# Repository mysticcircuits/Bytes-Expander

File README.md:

# Bytes-Expander
Variable Loop Length Turing Machine Expander

A 3rd party Turing Machine expander which allows for voltage control over the loop length of the host device.  It will require 
some modifications to the host Turing Machine which have only been tested with the Turing v1, but it is hypothetically
possible to modify the v2 to do accept the expander too.  There are instructions for the v1 modifications in the instructions
folder.

For questions or help building the module check out the relevant thread on MW.

http://www.muffwiggler.com/forum/viewtopic.php?p=1646194#1646194

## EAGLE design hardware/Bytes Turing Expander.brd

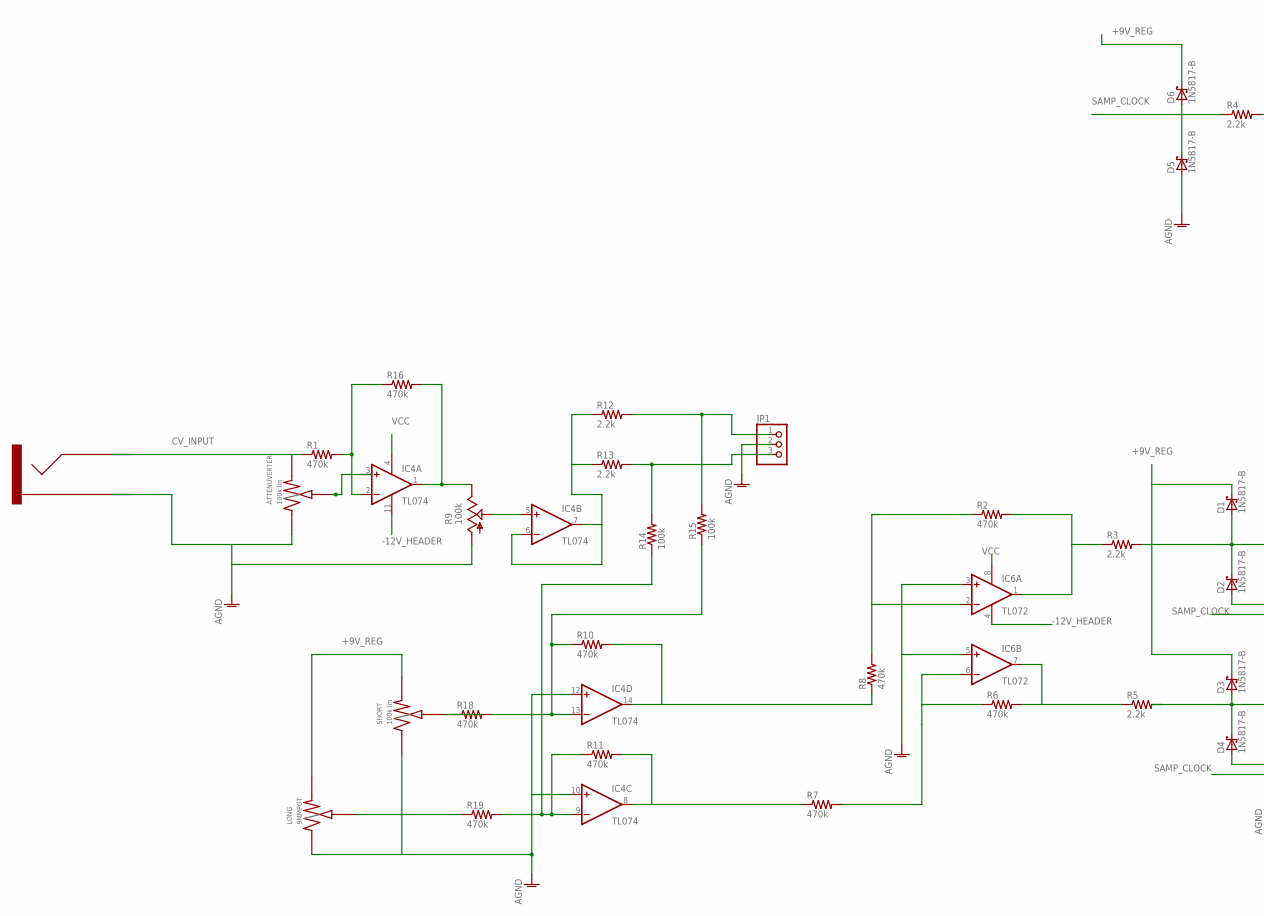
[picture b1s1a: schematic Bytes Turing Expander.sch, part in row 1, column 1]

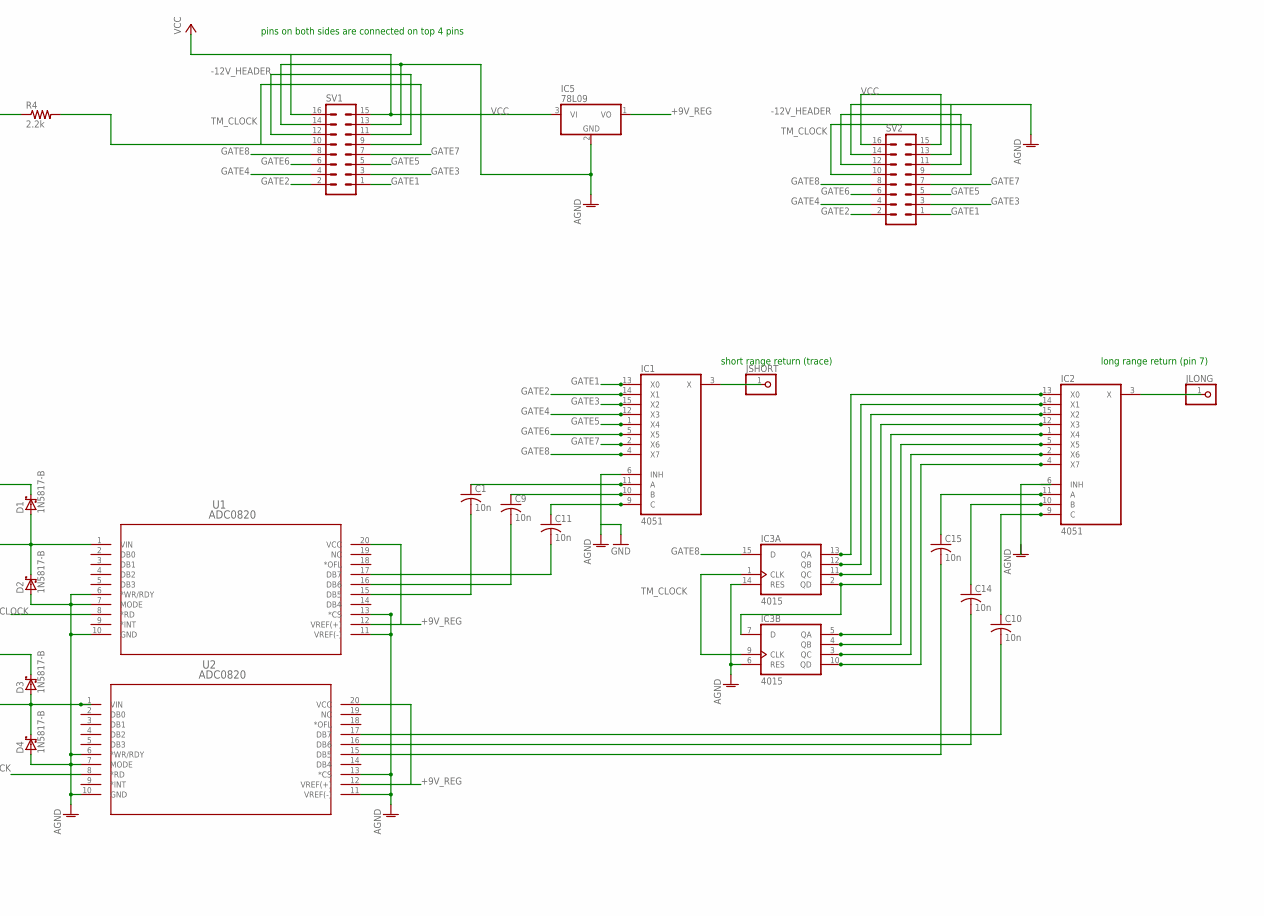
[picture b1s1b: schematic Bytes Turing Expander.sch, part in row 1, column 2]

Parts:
ATTENUVERTER: 100k lin; 9MMPOT
C1, C9, C10, C11, C14, C15: 10n; C025-024X044
D1, D2, D3, D4, D5, D6: 1N5817-B; DO41-7.6
IC1, IC2: 4051; DIL16
IC3: 4015; DIL16
IC4: TL074; DIL14
IC5: 78L09; TO92
IC6: TL072; DIL08
JLONG: PINHD-1X1; 1X01
JP1: PINHD-1X3; 1X03
JSHORT: PINHD-1X1; 1X01
LONG: 9MMPOT
R1, R2, R6, R7, R8, R10, R11, R16, R18, R19: 470k; 0204V
R3, R4, R5, R12, R13: 2.2k; 0204V
R9: 100k; B64Y
R14, R15: 100k; 0204V
SHORT: 100k lin; 9MMPOT
SV1, SV2: MA08-2
U1, U2: ADC0820; NFH20
U$1: 3.5MMJACK; 3.5MMPHONEJACK

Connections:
+9V_REG: D1.C, D3.C, D6.C, IC5.1 (VO), LONG.LEFT (RIGHT), SHORT.LEFT (RIGHT), U1.12 (VREF(+)), U1.20 (VCC), U2.12 (VREF(+)), U2.20 (VCC)
-12V_HEADER: IC4.11 (V-), IC6.4 (V-), SV1.11, SV1.12, SV2.11, SV2.12
AGND: ATTENUVERTER.RIGHT (LEFT), D2.A, D4.A, D5.A, IC1.6 (INH), IC1.7 (VEE), IC1.8 (GND), IC2.7 (VEE), IC2.8 (GND), IC3.6 (RES), IC3.14 (RES), IC4.10 (+IN), IC4.12 (+IN), IC5.2 (GND), IC6.3 (+IN), IC6.5 (+IN), JP1.2, LONG.RIGHT (LEFT), R9.A, SHORT.RIGHT (LEFT), SV1.13, SV1.14, SV2.13, SV2.14, U1.6 (*WR/RDY), U1.7 (MODE), U1.10 (GND), U1.11 (VREF(-)), U1.13 (*CS), U2.6 (*WR/RDY), U2.7 (MODE), U2.10 (GND), U2.11 (VREF(-)), U2.13 (*CS), U$1.SLEEVE
CV_INPUT: ATTENUVERTER.LEFT (RIGHT), R1.1, U$1.TIP
GATE1: IC1.13 (X0), SV1.1, SV2.1
GATE2: IC1.14 (X1), SV1.2, SV2.2
GATE3: IC1.15 (X2), SV1.3, SV2.3
GATE4: IC1.12 (X3), SV1.4, SV2.4
GATE5: IC1.1 (X4), SV1.5, SV2.5
GATE6: IC1.5 (X5), SV1.6, SV2.6
GATE7: IC1.2 (X6), SV1.7, SV2.7
GATE8: IC1.4 (X7), IC3.15 (D), SV1.8, SV2.8
JSHORT: IC1.3 (X), JSHORT.1
unnamed: IC4.2 (-IN), R1.2, R16.1
unnamed: IC4.1 (OUT), R9.E, R16.2
unnamed: LONG.CENTER, R19.1
unnamed: R18.1, SHORT.CENTER
unnamed: IC4.6 (-IN), IC4.7 (OUT), R12.1, R13.1
unnamed: IC4.5 (+IN), R9.S
unnamed: IC6.1 (OUT), R2.2, R3.1
unnamed: IC4.9 (-IN), R11.1, R14.1, R19.2
unnamed: IC2.12 (X3), IC3.2 (QD), IC3.7 (D)
unnamed: C11.1, IC1.9 (C)
unnamed: IC2.13 (X0), IC3.13 (QA)
unnamed: IC2.14 (X1), IC3.12 (QB)
unnamed: IC2.15 (X2), IC3.11 (QC)
unnamed: IC2.1 (X4), IC3.5 (QA)
unnamed: IC2.5 (X5), IC3.4 (QB)
unnamed: IC2.2 (X6), IC3.3 (QC)
unnamed: IC2.4 (X7), IC3.10 (QD)
unnamed: IC4.14 (OUT), R8.1, R10.2
unnamed: IC6.7 (OUT), R5.1, R6.2
unnamed: IC4.8 (OUT), R7.1, R11.2
unnamed: JP1.3, R13.2, R14.2
unnamed: C9.1, IC1.10 (B)
unnamed: C1.1, IC1.11 (A)
unnamed: C11.2, U1.17 (DB7)
unnamed: C9.2, U1.16 (DB6)
unnamed: C1.2, U1.15 (DB5)
unnamed: C10.1, IC2.9 (C)
unnamed: C15.1, IC2.11 (A)
unnamed: C14.1, IC2.10 (B)
unnamed: IC6.2 (-IN), R2.1, R8.2
unnamed: C15.2, U2.15 (DB5)
unnamed: C14.2, U2.16 (DB6)
unnamed: C10.2, U2.17 (DB7)
unnamed: JP1.1, R12.2, R15.2
unnamed: ATTENUVERTER.CENTER, IC4.3 (+IN)
unnamed: IC4.13 (-IN), R10.1, R15.1, R18.2
unnamed: IC6.6 (-IN), R6.1, R7.2
unnamed: IC2.3 (X), JLONG.1
unnamed: D3.A, D4.C, R5.2, U2.1 (VIN)
unnamed: D1.A, D2.C, R3.2, U1.1 (VIN)
SAMP_CLOCK: D5.C, D6.A, R4.1, U1.8 (*RD), U2.8 (*RD)
TM_CLOCK: IC3.1 (CLK), IC3.9 (CLK), R4.2, SV1.9, SV1.10, SV2.9, SV2.10
VCC: IC1.16 (VCC), IC2.16 (VCC), IC3.16 (VDD), IC4.4 (V+), IC5.3 (VI), IC6.8 (V+), SV1.15, SV1.16, SV2.15, SV2.16
VSS: IC3.8 (VSS)

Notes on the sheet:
short range return (trace)
long range return (pin 7)
pins on both sides are connected on top 4 pins

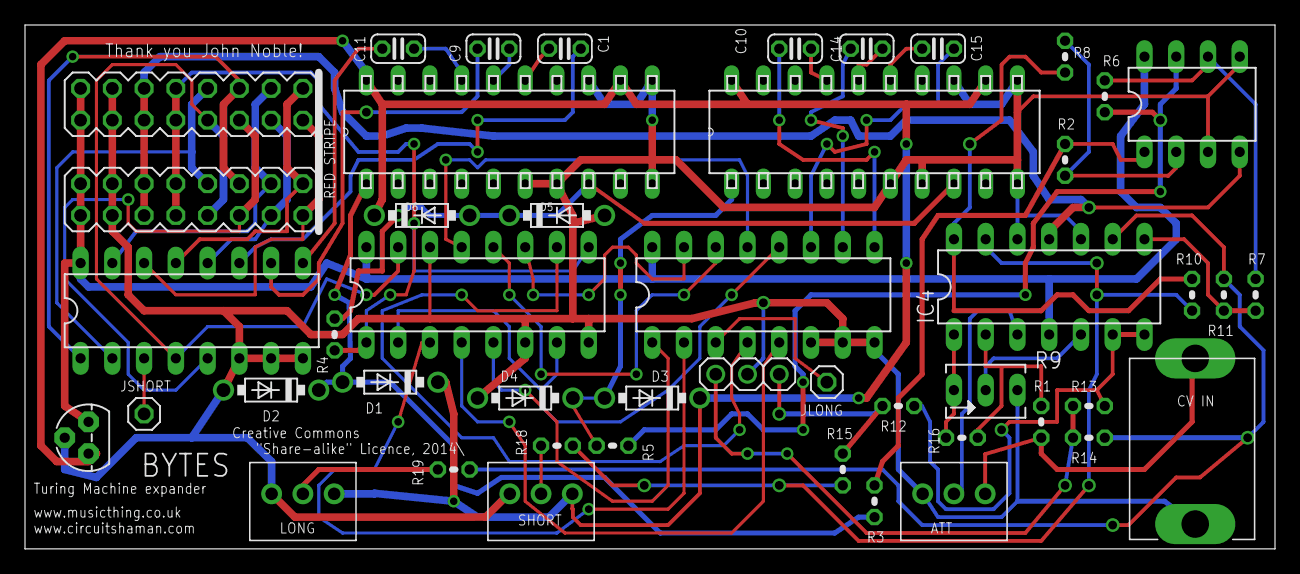
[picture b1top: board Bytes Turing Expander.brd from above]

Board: 2 copper layers, 100.0 x 41.9 mm, 47 parts (0 on the bottom side), 56 nets.

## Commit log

2019-05-06 Create dddd
2019-05-06 Create lkdjflskjfd

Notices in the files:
hardware/Bytes Turing Expander.brd:
Creative Commons
